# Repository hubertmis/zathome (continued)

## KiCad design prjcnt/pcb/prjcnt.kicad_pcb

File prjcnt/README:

Build with:

$ west build -b prjcnt -- -DBOARD_ROOT=$PWD -DSB_CONFIG_BOOT_SIGNATURE_KEY_FILE=\"$PWD/prjcnt.pem\" -Dprjcnt_COAPS_PSK=\"xxxx\"

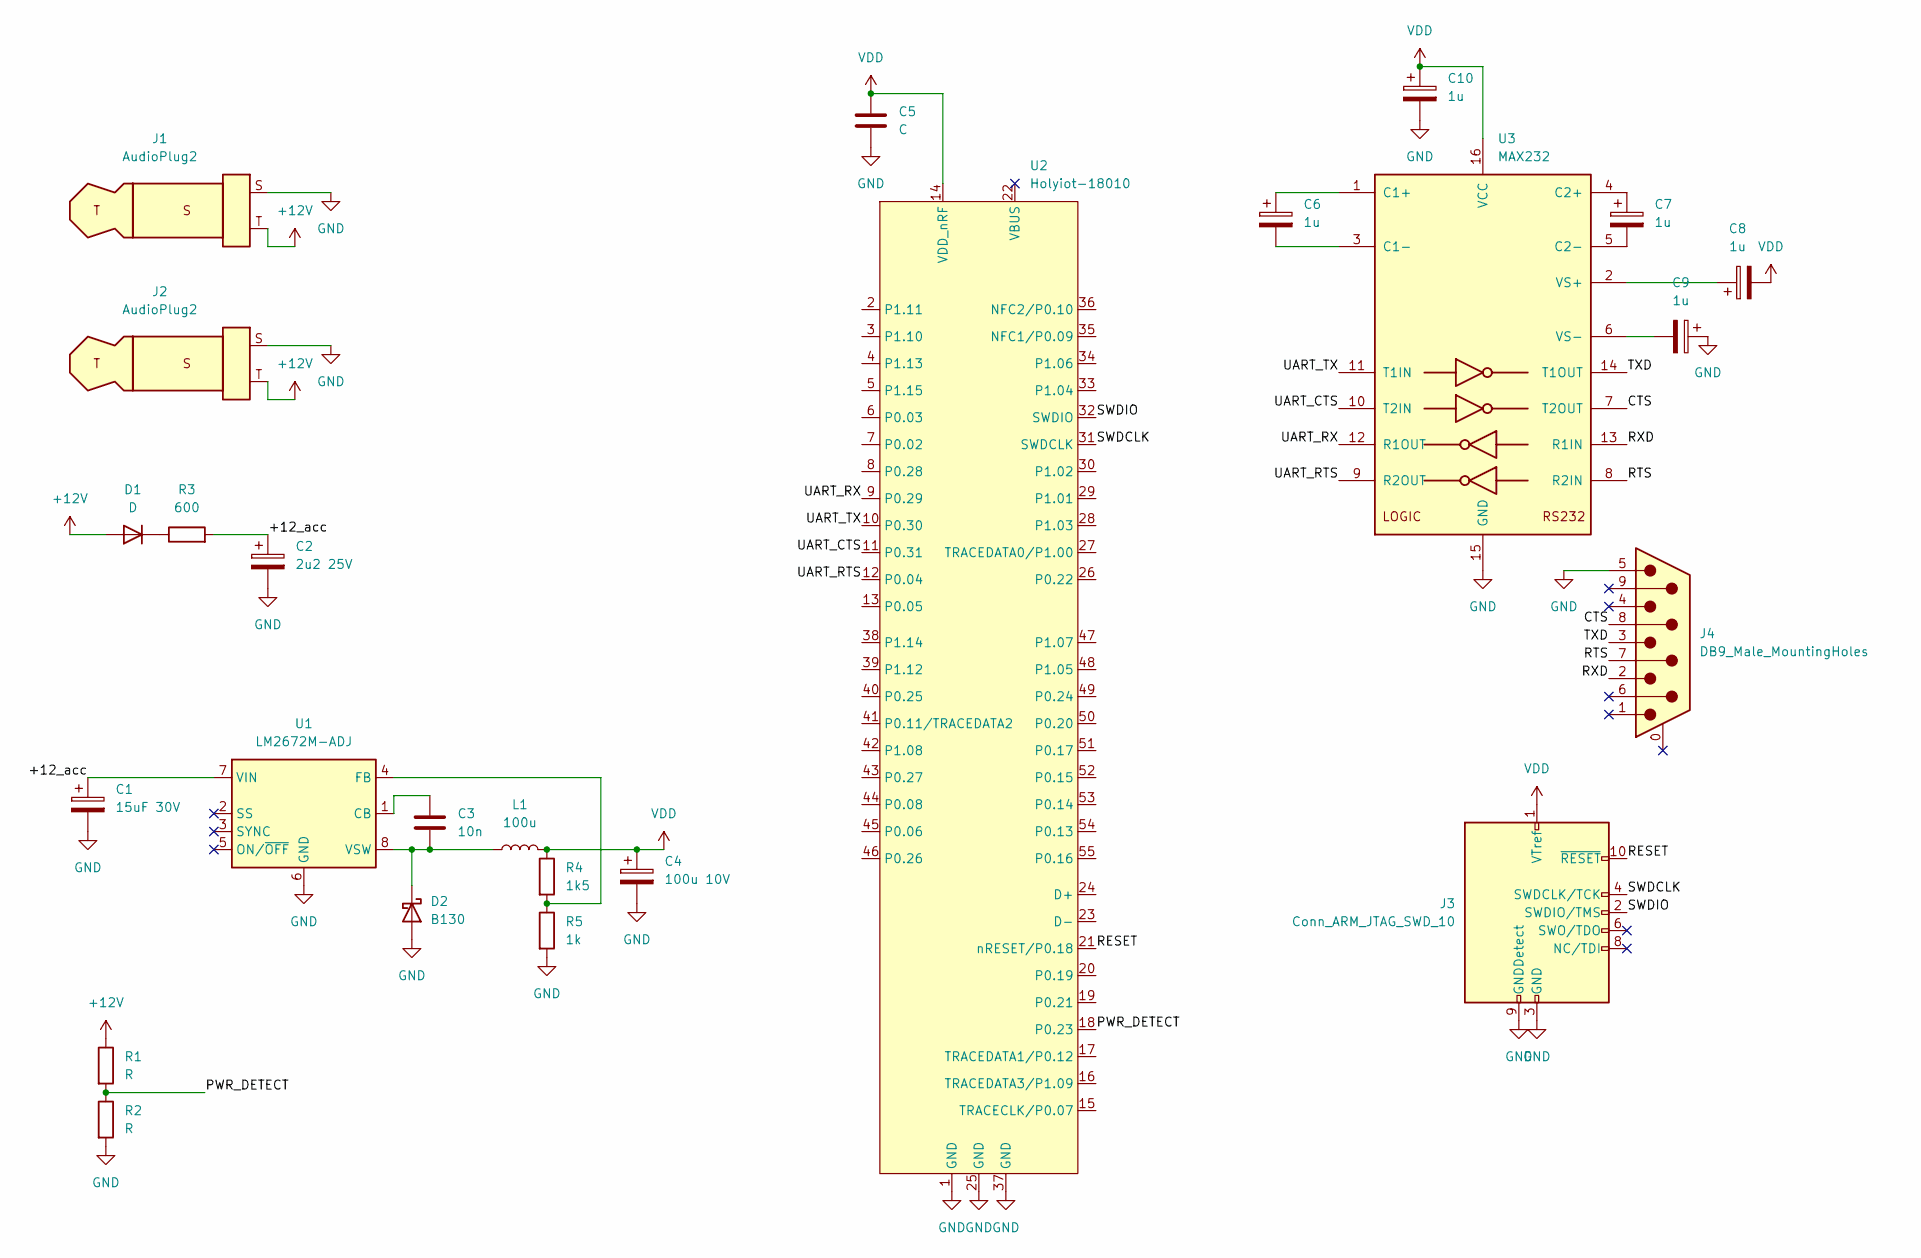
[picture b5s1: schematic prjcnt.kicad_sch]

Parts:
C1: 15uF 30V; CP_EIA-7343-31_Kemet-D_Pad2.25x2.55mm_HandSolder
C2: 2u2 25V; CP_Axial_L30.0mm_D18.0mm_P35.00mm_Horizontal
C3: 10n; C_0603_1608Metric_Pad1.08x0.95mm_HandSolder
C4: 100u 10V; CP_EIA-6032-28_Kemet-C_Pad2.25x2.35mm_HandSolder
C5: C; C_0603_1608Metric_Pad1.08x0.95mm_HandSolder
C6, C7, C8, C9, C10: 1u; CP_EIA-3216-18_Kemet-A_Pad1.58x1.35mm_HandSolder
D1: D; D_SOD-123
D2: B130; D_SMA-SMB_Universal_Handsoldering
J1, J2: AudioPlug2; Jack_3.5mm_Lumberg_1503_07_Horizontal
J3: Conn_ARM_JTAG_SWD_10; PinHeader_2x05_P1.27mm_Vertical_SMD
J4: DB9_Male_MountingHoles; DSUB-9_Male_Horizontal_P2.77x2.84mm_EdgePinOffset4.94mm_Hou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
L1: 100u; L_7.3x7.3_H3.5
R1, R2: R; R_0603_1608Metric_Pad0.98x0.95mm_HandSolder
R3: 600; R_0603_1608Metric_Pad0.98x0.95mm_HandSolder
R4: 1k5; R_0603_1608Metric_Pad0.98x0.95mm_HandSolder
R5: 1k; R_0603_1608Metric_Pad0.98x0.95mm_HandSolder
U1: LM2672M-ADJ; SOIC-8_3.9x4.9mm_P1.27mm
U2: Holyiot-18010
U3: MAX232; SSOP-16_5.3x6.2mm_P0.65mm

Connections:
+12V: D1.2 (A), J1.T, J2.T, R1.1
/+12_acc: C1.1, C2.1, R3.2, U1.7 (VIN)
/CTS: J4.8, U3.7 (T2OUT)
/PWR_DETECT: R1.2, R2.1, U2.18 (P0.23)
/RESET: J3.10 (~RESET), U2.21 (nRESET/P0.18)
/RTS: J4.7, U3.8 (R2IN)
/RXD: J4.2, U3.13 (R1IN)
/SWDCLK: J3.4 (SWDCLK/TCK), U2.31 (SWDCLK)
/SWDIO: J3.2 (SWDIO/TMS), U2.32 (SWDIO)
/TXD: J4.3, U3.14 (T1OUT)
/UART_CTS: U2.11 (P0.31), U3.10 (T2IN)
/UART_RTS: U2.12 (P0.04), U3.9 (R2OUT)
/UART_RX: U2.9 (P0.29), U3.12 (R1OUT)
/UART_TX: U2.10 (P0.30), U3.11 (T1IN)
GND: C1.2, C2.2, C4.2, C5.2, C9.1, C10.2, D2.2 (A), J1.S, J2.S, J3.3 (GND), J3.5 (GND), J3.9 (GNDDetect), J4.5, R2.2, R5.2, U1.6 (GND), U2.1 (GND), U2.25 (GND), U2.37 (GND), U3.15 (GND)
unnamed: C3.1, U1.1 (CB)
unnamed: C3.2, D2.1 (K), L1.1, U1.8 (VSW)
unnamed: C6.1, U3.1 (C1+)
unnamed: C6.2, U3.3 (C1-)
unnamed: C7.1, U3.4 (C2+)
unnamed: C7.2, U3.5 (C2-)
unnamed: C8.1, U3.2 (VS+)
unnamed: C9.2, U3.6 (VS-)
unnamed: D1.1 (K), R3.1
unnamed: R4.2, R5.1, U1.4 (FB)
VDD: C4.1, C5.1, C8.2, C10.1, J3.1 (VTref), L1.2, R4.1, U2.14 (VDD_nRF), U3.16 (VCC)

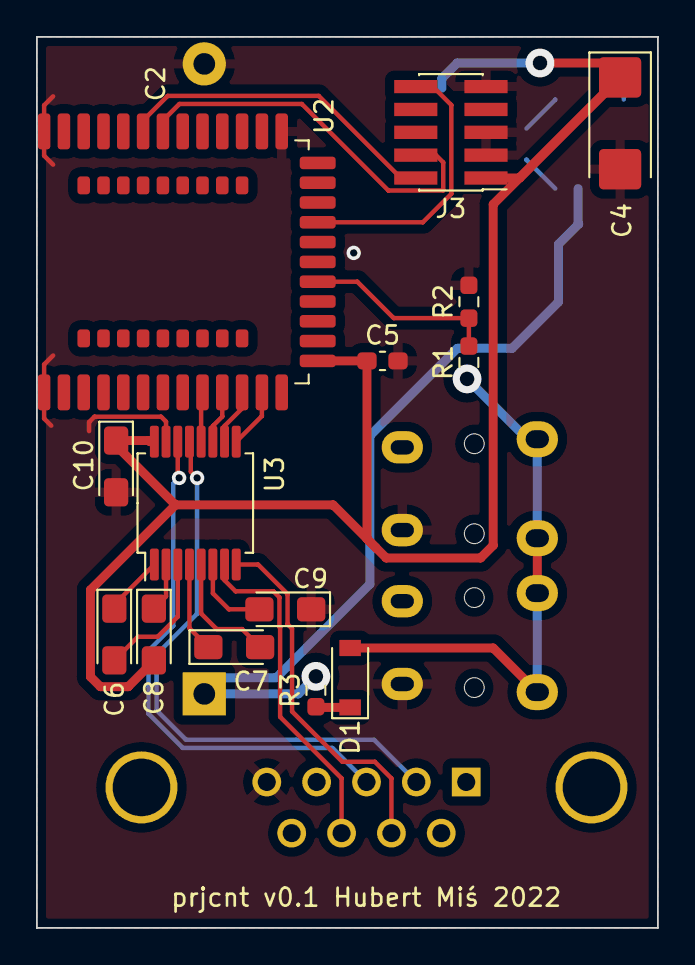
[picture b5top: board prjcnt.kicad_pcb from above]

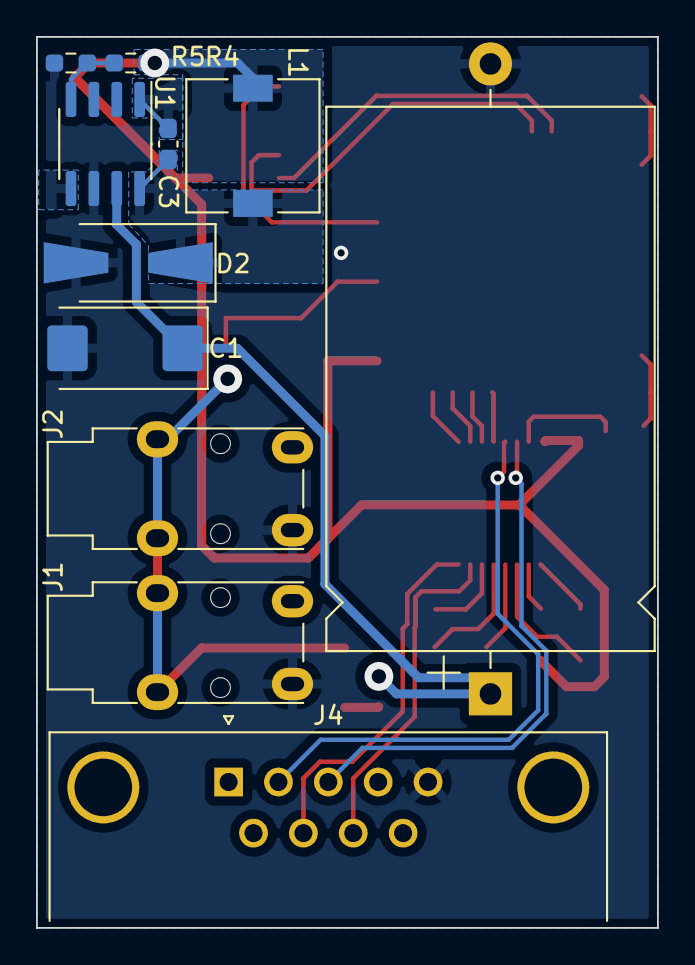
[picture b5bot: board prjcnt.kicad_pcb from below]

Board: 2 copper layers, 34.5 x 49.5 mm, 25 parts (11 on the bottom side), 26 nets.

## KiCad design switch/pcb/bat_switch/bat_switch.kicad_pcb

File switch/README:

Build with:

$ west build -b switch -- -DBOARD_ROOT=$PWD -DSB_CONFIG_BOOT_SIGNATURE_KEY_FILE=\"$PWD/switch.pem\" -Dswitch_COAPS_PSK=\"xxxx\"
$ west build -b bat_switch -- -DBOARD_ROOT=$PWD -DSB_CONFIG_BOOT_SIGNATURE_KEY_FILE=\"$PWD/bat_switch.pem\" -Dbat_switch_COAPS_PSK=\"xxxx\"

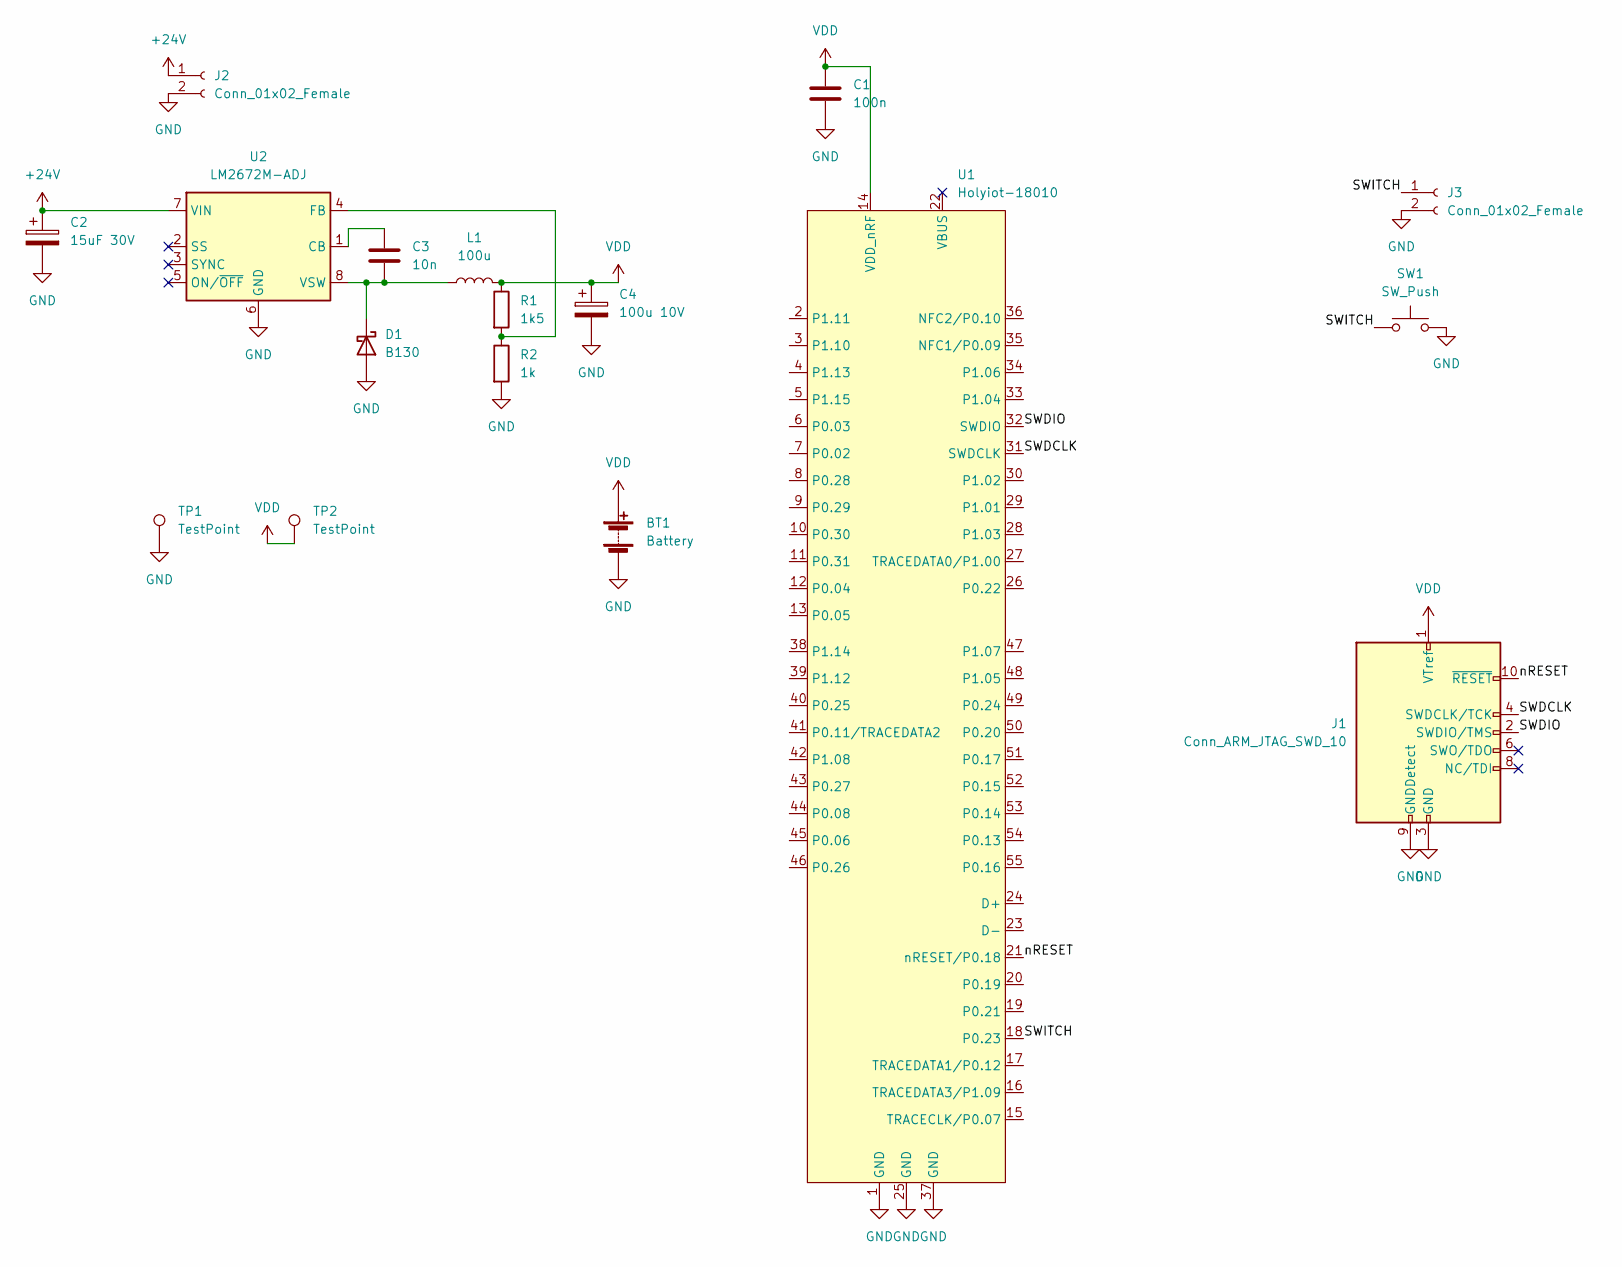
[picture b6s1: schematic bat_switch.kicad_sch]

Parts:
BT1: Battery; PinSocket_2x01_P2.54mm_Vertical_SMD
C1: 100n; C_0603_1608Metric_Pad1.08x0.95mm_HandSolder
C2: 15uF 30V; CP_EIA-7343-31_Kemet-D_Pad2.25x2.55mm_HandSolder
C3: 10n; C_0603_1608Metric_Pad1.08x0.95mm_HandSolder
C4: 100u 10V; CP_EIA-6032-28_Kemet-C_Pad2.25x2.35mm_HandSolder
D1: B130; D_SMA-SMB_Universal_Handsoldering
J1: Conn_ARM_JTAG_SWD_10; PinHeader_2x05_P1.27mm_Vertical_SMD
J2, J3: Conn_01x02_Female; JST_NV_B02P-NV_1x02_P5.00mm_Vertical
L1: 100u; L_7.3x7.3_H3.5
R1: 1k5; R_0603_1608Metric_Pad0.98x0.95mm_HandSolder
R2: 1k; R_0603_1608Metric_Pad0.98x0.95mm_HandSolder
SW1: SW_Push; SW_Push_1P1T_NO_CK_PTS125Sx43PSMTR
TP1, TP2: TestPoint; TestPoint_Pad_D1.0mm
U1: Holyiot-18010
U2: LM2672M-ADJ; SOIC-8_3.9x4.9mm_P1.27mm

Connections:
+24V: C2.1, J2.1, U2.7 (VIN)
/SWDCLK: J1.4 (SWDCLK/TCK), U1.31 (SWDCLK)
/SWDIO: J1.2 (SWDIO/TMS), U1.32 (SWDIO)
/SWITCH: J3.1, SW1.1, U1.18 (P0.23)
/nRESET: J1.10 (~RESET), U1.21 (nRESET/P0.18)
GND: BT1.2 (-), C1.2, C2.2, C4.2, D1.2 (A), J1.3 (GND), J1.5 (GND), J1.9 (GNDDetect), J2.2, J3.2, R2.2, SW1.2, TP1.1, U1.1 (GND), U1.25 (GND), U1.37 (GND), U2.6 (GND)
unnamed: C3.1, U2.1 (CB)
unnamed: R1.2, R2.1, U2.4 (FB)
unnamed: C3.2, D1.1 (K), L1.1, U2.8 (VSW)
VDD: BT1.1 (+), C1.1, C4.1, J1.1 (VTref), L1.2, R1.1, TP2.1, U1.14 (VDD_nRF)

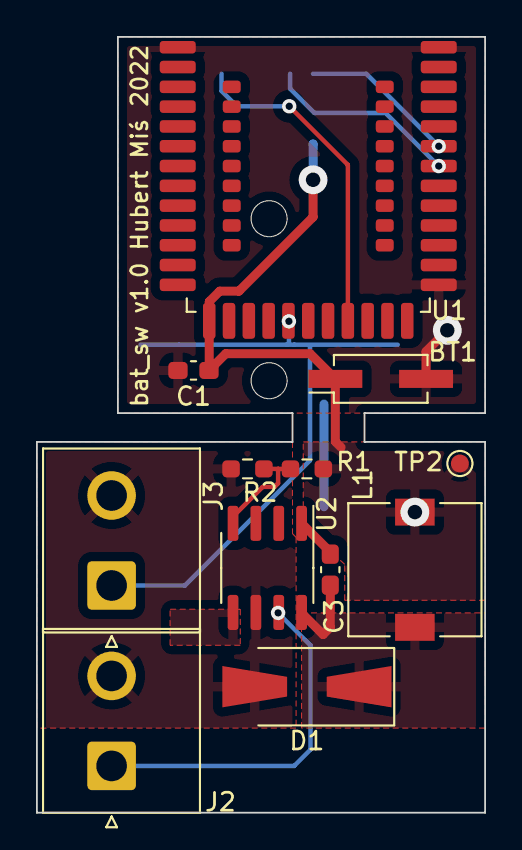
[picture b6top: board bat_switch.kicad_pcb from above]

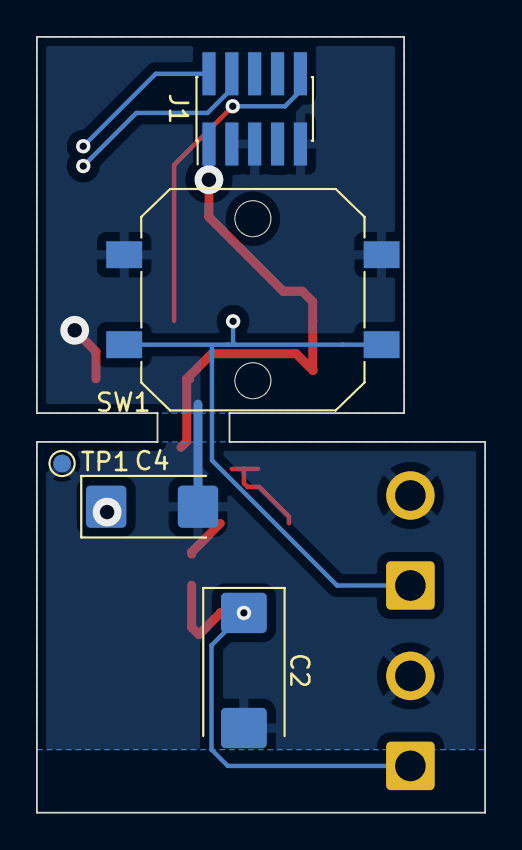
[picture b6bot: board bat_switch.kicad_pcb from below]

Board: 2 copper layers, 24.9 x 43.1 mm, 17 parts (5 on the bottom side), 10 nets.

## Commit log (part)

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2020-12-28 Basic temperature touchscreen based on Zephyr
    At this stage functional features are:
    * display with touch support
    * NTC temperature sensor
    * relay controller
    * basic connectivity including FOTA
2021-01-16 Update NTC to use nRF SAADC driver properly
    SAADC requires special configuration of positive input selection
2021-01-23 Update variables in bootstrap script
2021-01-23 Use correct temperature sensor to control relay output
2021-01-23 Initial CoAP services using target Zephyr implementation
2021-01-23 Temporary remove unused fields from FT800 devicetree
2021-01-24 Update to NCS 2021-01-24
    NCS commit SHA: 314ccaf0d90e0fd81562058544d42b51262f3109
2021-01-25 CoAP temperature settings setter
2021-01-30 Replace OpenThread CoAP with Zephyr CoAP
2021-01-30 Provisioning service
    This service is planned to be used to set CoAP resources
    used by other services
2021-01-31 Fix overflow in PWM output
2021-01-31 Second CoAP temperature resource
    This patch adds CoAP access to second temperature sensor in the device
2021-02-02 CoAP Service Discovery server
2021-02-06 Service Discovery server and client
2021-02-06 Experimental secure socket
2021-02-07 Start coaps server automatically
2021-02-07 Preparation to forbid access based on address scope or security
2021-02-07 Fix Thread Joiner role while coaps server is enabled.
    It seems more mbedtls heap is required in such configuration.
2021-02-07 Don't display local temperature setting if output is unavailable
2021-03-06 Add screensaver displaying clock
2021-03-10 Reduce brightness of clock screensaver
2021-03-10 Update default controller parameters
2021-03-10 Fix race condition in touchscreen processing
    Touch detection interrupt must wake up touch processing thread to get
    next touch event value. Previously the interrupt simply invoked wake
    up call. But there was a race condition when touch event was triggered
    after the thread has read the interrupt reason, but before the tread
    fell asleep. In such conditions, interrupt pin was asserted what
    caused the interrupt and wake up call that had no effects, because
2021-03-26 Discover ventilation service in the network
2021-03-30 Select discovery scope depending on service placement
2021-04-08 Skeleton of RGBW firmware
2021-05-02 Initial CoAP connection for RGBW application
2021-06-20 Enable FOTA in RGBW application
2021-07-18 Add provisioning data store to RGBW application
2021-07-18 Add CoAP GET command of LEDs status to RGBW application
2021-07-18 Add CoAP POST command of LEDs status to RGBW application
2021-07-18 Add CoAP Service Discovery server to RGBW application
2021-10-10 shcnt app skeleton
2021-10-11 shcnt: test of relay driver
2021-10-11 shcnt: initial motor controller implementation
2021-10-12 shcnt: add stop function to motor controller
2021-10-17 shcnt: add setting target between boundaries
2021-10-17 shcnt: Enable hight tx power and ff05::1 address
2021-10-17 shcnt: Add provisioning module
2021-10-17 shcnt: provisioning CoAP commands
2021-10-17 shcnt: add CoAP fota commands
2021-10-18 shcnt: CoAP commands to set motion duration and get position
2021-10-23 shcnt: CoAP commands to run motor
2021-10-23 shcnt: add heartbeat led, verify FOTA
2021-11-06 shcnt: deployment, compatible with shrmt
2021-11-07 shcnt: position service as a framework for position override feature
2021-11-07 shcnt: new feature: full swing in regular intervals
2021-11-13 Mass deployment version
2022-01-13 shcnt: Update touchscreen experience in clock screen
2022-01-17 New application: switch: initial version with Thread connectivity
2022-01-17 temptscrn: remove unnecessary declarations from coap.h
2022-01-17 shcnt: do not start motor if already in extreme position
2022-01-19 rgbw: update to NCS 1.8.0
2022-01-22 rgbw: polynomial approxymation of PWM pulse width
2022-01-22 switch: Request preset settings from actuators
2022-01-22 rgbw: smooth color changing
2022-01-30 accnt: Daikin S21 commands enc/dec skeleton
2022-01-30 accnt: LEDs indicating UART connection status
2022-01-30 accnt: CoAP commands to pass UART frames
2022-01-30 accnt: create custom board description
2022-02-20 accnt: CoAP main resource getter
2022-02-20 project: Ignore PCB fab output files in version control system
2022-02-20 accnt: Prepare PCB for production
2022-02-20 switch: new PCB for battery or DC powered switch
2022-05-07 accnt: fix missing GND connection in PCB
2022-05-21 accnt: Add CoAP command for basic state of AC unit
2022-05-21 accnt: Handle CoAP resource getter when serial returns an error
2022-05-21 accnt: Handle disabled AC mode in CoAP state getter
2022-06-25 accnt: Temperature getter and some fixes in CoAP module
2022-07-05 switch: Use ADC as an alternate switch detection
    It looks some light switches do not disconnect electrical circuit but
    increase their impedance instead. Impedance is low enough to keep
    transoptor active, but with lower intensity than when the switch is
    on. Transoptor intensity is detected with ADC and changes in intensity
    treated as switch events.
2022-07-11 switch: store analog threshold in provisioning data
2022-07-11 temp_tscrn: Remove debug data, code cleanup
2022-07-14 temptscrn: fix bedroom spelling in the menu label
2022-07-16 temptscrn: fixes in light related screens
    Fix spelling error in menu.
    Invert sliders and modify their colors in light control screen.
2022-07-18 temp_tscrn: use common continuous_sd for ventilation service discovery
2022-07-18 temp_tscrn: add continuous_sd debugging coap command
2022-07-19 temp_tscrn: cleanup in coap module
2022-07-20 temp_tscrn: fix dynamic coap resources
2022-07-21 temp_tscrn: coap and cbor refactoring
    Extract common code parts to utility functions
2022-07-21 temp_tscrn: use continuous_sd service to discover remote output resource
2022-07-26 rgbw: refactoring of CoAP module
2022-07-26 shcnt: refactor coap module to use common utilities
2022-07-31 Fix recursion but in simple coap setter function
2022-07-31 Add "Method Not Allowed" response to CoAP response handler
2022-08-01 rgbw: Fix setting green color manually
2022-08-01 rgbw: add coap command to reset manual settings
2022-08-01 rgbw: add temporary dimmer feature
2022-08-02 rgbw: Fix setting green color automatically
2022-09-09 prjcnt: version initially tested on a nRF2840-DK
2022-09-09 rgbw: input from prjcnt
2022-09-10 rgbw: rewrite led controller to rely on timestamps instead of FSM
    The state machine was pretty complicated. Timestamps make the algorithm
    much simpler and extensible.
2022-09-23 rgbw: fix manual animation timing
    Manual animation timing is correct if dimmer is disabled. Without
    this patch manual animation took dimmer timing if manually selected
    setting was equal to dimmed.
2022-09-23 prjcnt: remove temp kicad filex
2022-09-25 FTDs: fix building - add missing functions to a header file
2022-09-25 coap_server fix: do not reply with 4.04 for NON messages
2022-09-25 shcnt: add projector handler
    When projector is enabled close the shades.
    It should apply only from dusk to dawn, but time of day handler is not
    available yet
2022-09-27 rgbw: update version number to 0.1.0
2022-09-27 prjcnt: number of notification sinks is easily configurable
2022-10-02 prjcnt: a few bug fixes for the first deployed version
2022-10-15 shcnt: fix restoring previous position after projector is disabled
2022-10-15 prjcnt: extend scope of service discovery to whole site
2022-10-15 rgbw: fixes in restoring setting after the projector is disabled
2022-10-24 temptscrn: fix projector location for coap resources
2022-10-24 temp_tscrn: add more debug data for continuous_sd module
2022-11-08 switch: add bat_switch board
    bat_switch board includes single monostable switch and none analog
    switches
2022-11-21 temp_tscrn: add more debug data to cont_sd module
2022-11-21 lib: continuous_sd: fix calculation of timeout expiration
    Continuous sd process hang on timeout expiration because of a bug
    causing the thread to enter infinite loop condition. Now timeout
    handling should be working correctly.
2023-05-21 switch: Fixed service discovery
    Updating common libraries fixed service discovery for switch node
2024-01-20 shcnt: lower mot_cnt thread priority
    Disallow mot_cnt threads malfunction from breaking CoAP communication
2024-01-20 shcnt: refactor mot_cnt
    Make mot_cnt.c module cleaner
2024-01-20 shcnt: fix hanging mot_cnt thread
    The mot_cnt thread hang if the requested target position was equal
    to the current position. In this case the thread stopped the movement
    and acted like a new requested interrupted ongoing movement: reevaluated
    the target, stopped the movement again, and acted like a new request
    interrupted ongoing movement...
    Instead of acting like a new request interrupts the ongoing movement,
2024-07-14 temp_tscrn: new power pcb
    Use SSRs instead of a relay
2024-07-16 temp_tscrn: add shades control
2024-07-16 shcnt: skip recalculating position if continuing movement
    Each position recalculation increases uncertainty. It's better to
    avoid recalcuation until the movement is stopped
2024-08-04 bat_sw: fix SED operations
2024-09-22 switch: battery-powered sends non confirmable requests
2024-09-23 Add CoAP option to suppress awaiting responses
2024-10-16 rgbw: presets provisioning
2024-12-01 Porting to NCS 2.7.
    Partially temp_tscrn is ported
2024-12-07 It's building. Did not program yet
2024-12-11 wip: pinging state, but UDP hangs networking
2024-12-26 temp_tscn: porting to NCS 2.8.0, fota almost working
    There is still a problem around initializing CoAP download in the
    download_client
2024-12-27 temp_tscrn: fota working with NCS 2.8.0
    shades_conn threads must be disabled, they fail because of an unknown reason
2025-01-05 Fix filtering service discovery requests and used cbor utils
2025-01-08 temp_tscrn: port to NCS 2.8 including most of the libs
    It also addes nRF52840-DK as a build target
2025-01-08 temp_tscrn: shades control improvements
    Display multiple shades bars in a single screen and fix CoAP
    operations around controlling shades.
2025-01-10 temp_tscrn: Fix relay control
    While porting to NCS 2.8 the relay control got broken because of invalid
    API alignment. Now it's fixed.
    Moreover, the projector and manual forced switching of the relay are
    cleaned up
2025-04-26 vlvts: Introduce thermal valve control system
    This introduction includes PCB design using Holyiot nRF52840 module
    intended to fit inside Moes Zigbee TRV 3.0 (ZTRV-BY-100-WH-MS) case
2025-04-26 temp_tscrn: update pcb gerber files
    Regenerage PCB gerber files including a place for a linear
    voltage regulator to be used if the main PCB is not to be
    modified.
2025-08-13 temp_tscrn: nit fixes
2025-08-13 prjcnt: port to NCS 2.8
2025-09-26 shcnt: port to NCS 2.8
2025-09-27 shcnt: fix port to zcbor
    zcbor map searching is greedy. If a key was found it may not be found
    again during subsequent searches. Extracting values from maps is
    refactored to allow find the key once and inspect the value type
    multiple times for the same key.
2025-11-30 temp_tscrn: pcb v3
    Version 3 of power supply for temp_tscrn PCB. This one uses triac and
    optotriac to control the heater
2025-11-30 gitignore: zip
    Add zip files to gitignore to avoid storing pcb gerber archives in the
    repository
2026-05-10 switch: update pcb
2026-05-10 vlvts: new pcb
2026-05-10 temp_tscrn: use a triac instead of a relay
2026-05-12 Add NCS 3.3.0 dependency in a west manifest
    Update shcnt and temp_tscrn to NCS 3.3.0
2026-06-20 commissioning: add cheat-sheet of the commissioning commands
